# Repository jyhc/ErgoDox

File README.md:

# Information
This repo is a fork of the Ergodox project https://github.com/Ergodox-io/ErgoDox to experiement with PCB modification to support Kailh choc low profile switches. 

Kailh choc footprint taken and modified from https://github.com/ebastler/marbastlib

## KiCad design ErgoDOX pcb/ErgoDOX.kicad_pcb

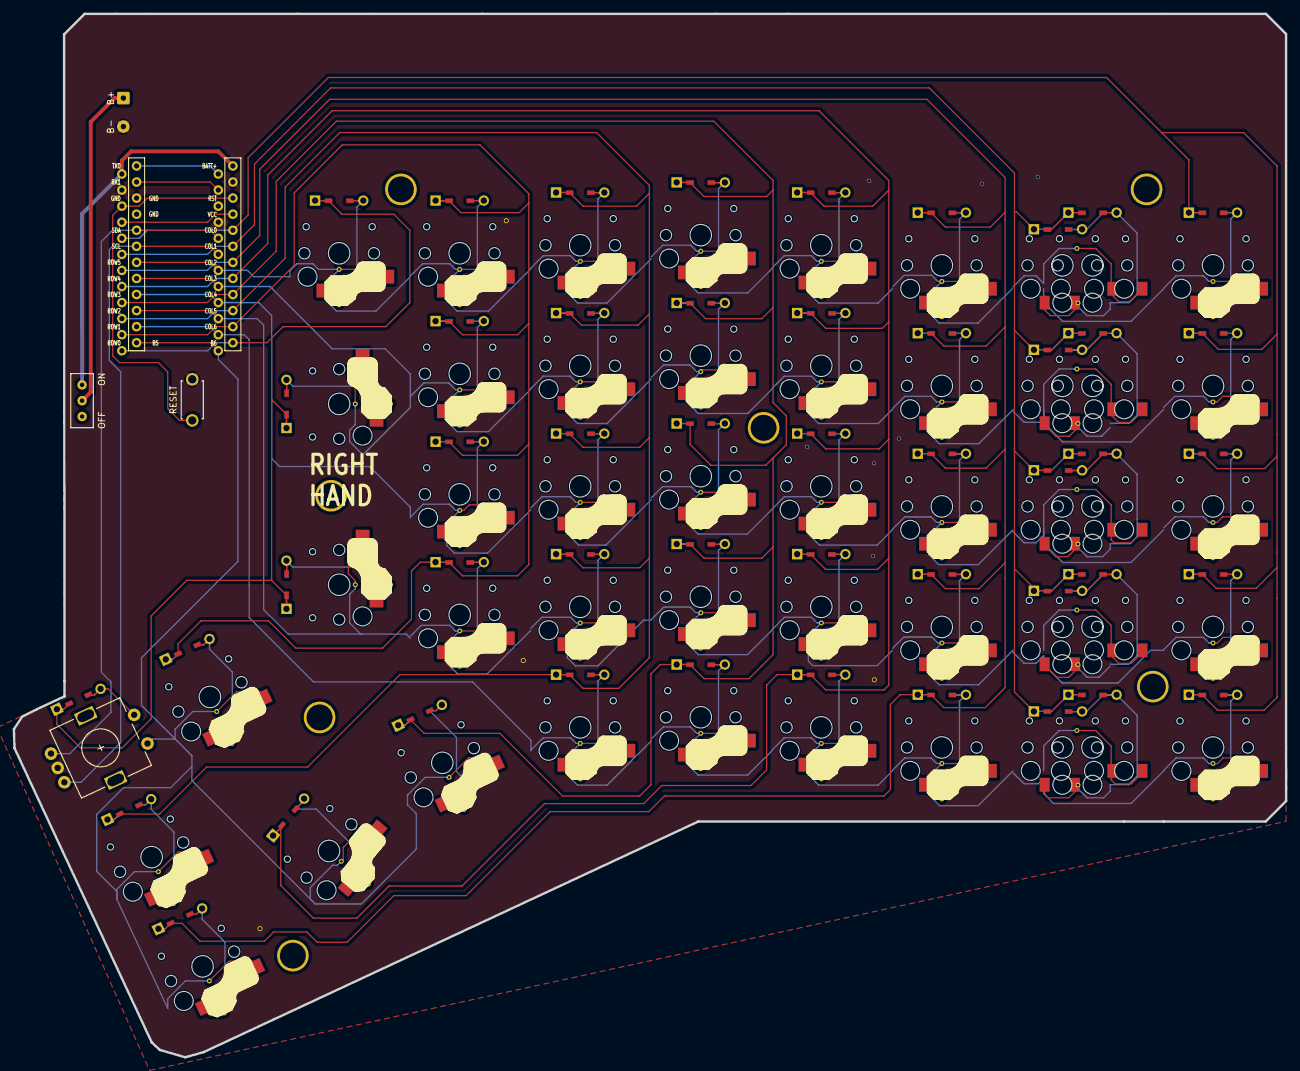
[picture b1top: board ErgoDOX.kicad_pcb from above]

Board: 2 copper layers, 201.1 x 164.9 mm, 51 parts (0 on the bottom side), 62 nets.

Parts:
BATTERY: Battery_Wire_Connector
BSW1: SW_DPDT_x2; SS-12D00
RSW1: SW_Push; ResetSW
STITCHING_VIA: STITCHING_VIA
STITCHING_VIA#2, STITCHING_VIA#3, STITCHING_VIA#4: STITCHING_VIA
SW0:7: SW0:6; RotaryEncoder_Alps_EC11E-Switch_Vertical_H20mm-keebio_modif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
SW0:8: SW0:5; Choc_Hotswap
SW0:9: SW0:4; Choc_Hotswap
SW0:10: SW0:3; Choc_Hotswap
SW0:11: SW0:2; Choc_Hotswap
SW0:12: SW0:1; Choc_Hotswap
SW1:9: SW1:4; Choc_Hotswap
SW1:10: SW1:3; Choc_Hotswap
SW1:11: SW1:2; Choc_Hotswap
SW1:12: SW1:1; Choc_Hotswap
SW1:13: SW1:0; Choc_Hotswap_1u+1.5u
SW2:7: SW2:6; Choc_Hotswap
SW2:8: SW2:5; Choc_Hotswap
SW2:9: SW2:4; Choc_Hotswap
SW2:10: SW2:3; Choc_Hotswap
SW2:11: SW2:2; Choc_Hotswap
SW2:12: SW2:1; Choc_Hotswap
SW2:13: SW2:0; Choc_Hotswap_1u+1.5u
SW3:8: SW3:5; Choc_Hotswap
SW3:9: SW3:4; Choc_Hotswap
SW3:10: SW3:3; Choc_Hotswap
SW3:11: SW3:2; Choc_Hotswap
SW3:12: SW3:1; Choc_Hotswap
SW3:13: SW3:0; Choc_Hotswap_1u+1.5u
SW4:7: SW4:6; Choc_Hotswap
SW4:8: SW4:5; Choc_Hotswap
SW4:9: SW4:4; Choc_Hotswap
SW4:10: SW4:3; Choc_Hotswap
SW4:11: SW4:2; Choc_Hotswap
SW4:12: SW4:1; Choc_Hotswap
SW4:13: SW4:0; Choc_Hotswap_1u+1.5u
SW5:7: SW5:6; Choc_Hotswap
SW5:8: SW5:5; Choc_Hotswap
SW5:9: SW5:4; Choc_Hotswap
SW5:10: SW5:3; Choc_Hotswap
SW5:11: SW5:2; Choc_Hotswap
SW5:12: SW5:1; Choc_Hotswap
SW5:13: SW5:0; Choc_Hotswap_1u+1.5u
SW11, SW11#2, SW11#3, SW11#4, SW11#5: SW_Push; Choc_Hotswap
U1: nice!nano; nicenano

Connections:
1-pad2: SW11#3.2, SW11#3.3
2-pad2: SW11#2.2, SW11#2.3
3-pad2: SW11#5.2, SW11#5.3
4-pad2: SW11.2, SW11.3
5-pad2: SW11#4.2, SW11#4.3
+BATT: BSW1.3, U1.24
/COL0: SW1:13.4 (K), SW2:13.4 (K), SW3:13.4 (K), SW4:13.4 (K), SW5:13.4 (K), U1.19
/COL1: SW0:12.4 (K), SW1:12.4 (K), SW2:12.4 (K), SW3:12.4 (K), SW4:12.4 (K), SW5:12.4 (K), U1.18
/COL4: SW0:9.4 (K), SW1:9.4 (K), SW2:9.4 (K), SW3:9.4 (K), SW4:9.4 (K), SW5:9.4 (K), U1.15
/COL5: SW0:8.4 (K), SW2:8.4 (K), SW3:8.4 (K), SW4:8.4 (K), SW5:8.4 (K), U1.14
/COL6: SW2:7.4 (K), SW4:7.4 (K), SW5:7.4 (K), U1.13
/COL7: SW11.4, SW11#2.4, SW11#3.4, SW11#4.4, SW11#5.4, U1.20
/COL10: SW0:10.4 (K), SW1:10.4 (K), SW2:10.4 (K), SW3:10.4 (K), SW4:10.4 (K), SW5:10.4 (K), U1.16
/COL11: SW0:11.4 (K), SW1:11.4 (K), SW2:11.4 (K), SW3:11.4 (K), SW4:11.4 (K), SW5:11.4 (K), U1.17
/ROW0: SW0:7.S1, SW0:8.1, SW0:9.1, SW0:10.1, SW0:11.1, SW0:12.1, U1.12
/ROW1: SW1:9.1, SW1:10.1, SW1:11.1, SW1:12.1, SW1:13.1, SW11#4.1, U1.11
/ROW2: SW2:7.1, SW2:8.1, SW2:9.1, SW2:10.1, SW2:11.1, SW2:12.1, SW2:13.1, SW11.1, U1.10
/ROW3: SW3:8.1, SW3:9.1, SW3:10.1, SW3:11.1, SW3:12.1, SW3:13.1, SW11#5.1, U1.9
/ROW4: SW4:7.1, SW4:8.1, SW4:9.1, SW4:10.1, SW4:11.1, SW4:12.1, SW4:13.1, SW11#2.1, U1.8
/ROW5: SW5:7.1, SW5:8.1, SW5:9.1, SW5:10.1, SW5:11.1, SW5:12.1, SW5:13.1, SW11#3.1, U1.7
/RST: RSW1.2, U1.22
ENCA: SW0:7.A, U1.5
ENCB: SW0:7.B, U1.6
GND: BATTERY.2, RSW1.1, STITCHING_VIA.GND, STITCHING_VIA#2.GND, STITCHING_VIA#3.GND, STITCHING_VIA#4.GND, SW0:7.C, U1.3, U1.4, U1.23
NET-(BSW1-PAD2): BATTERY.1, BSW1.2
unnamed: SW0:8.2, SW0:8.3 (A)
unnamed: SW0:9.2, SW0:9.3 (A)
unnamed: SW0:10.2, SW0:10.3 (A)
unnamed: SW0:11.2, SW0:11.3 (A)
unnamed: SW0:12.2, SW0:12.3 (A)
unnamed: SW1:9.2, SW1:9.3 (A)
unnamed: SW1:10.2, SW1:10.3 (A)
unnamed: SW1:11.2, SW1:11.3 (A)
unnamed: SW1:12.2, SW1:12.3 (A)
unnamed: SW1:13.2, SW1:13.3 (A)
unnamed: SW2:7.2, SW2:7.3 (A)
unnamed: SW2:8.2, SW2:8.3 (A)
unnamed: SW2:9.2, SW2:9.3 (A)
unnamed: SW2:10.2, SW2:10.3 (A)
unnamed: SW2:11.2, SW2:11.3 (A)
unnamed: SW2:12.2, SW2:12.3 (A)
unnamed: SW2:13.2, SW2:13.3 (A)
unnamed: SW3:8.2, SW3:8.3 (A)
unnamed: SW3:9.2, SW3:9.3 (A)
unnamed: SW3:10.2, SW3:10.3 (A)
unnamed: SW3:11.2, SW3:11.3 (A)
unnamed: SW3:12.2, SW3:12.3 (A)
unnamed: SW3:13.2, SW3:13.3 (A)
unnamed: SW4:7.2, SW4:7.3 (A)
unnamed: SW4:8.2, SW4:8.3 (A)
unnamed: SW4:9.2, SW4:9.3 (A)
unnamed: SW4:10.2, SW4:10.3 (A)
unnamed: SW4:11.2, SW4:11.3 (A)
unnamed: SW4:12.2, SW4:12.3 (A)
unnamed: SW4:13.2, SW4:13.3 (A)
unnamed: SW5:7.2, SW5:7.3 (A)
unnamed: SW5:8.2, SW5:8.3 (A)
unnamed: SW5:9.2, SW5:9.3 (A)
unnamed: SW5:10.2, SW5:10.3 (A)
unnamed: SW5:11.2, SW5:11.3 (A)
unnamed: SW5:12.2, SW5:12.3 (A)
unnamed: SW5:13.2, SW5:13.3 (A)

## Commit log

2022-05-21 test replace with choc switch
2022-05-22 add and modified Kailh choc footprint from https://github.com/ebastler/marbastlib
2022-05-22 replace first row switches
2022-05-23 finish replacing all switches
2022-05-28 add usb c footprint file from https://github.com/ai03-2725/Type-C.pretty
2022-05-29 change to usb c single side
2022-06-12 update with reroute to use nice nano v2 and choc hotswap footprint
2022-06-13 good for prod
2022-07-03 update holes
2022-07-20 create 1u1.5u footprint
2022-07-22 Revert "create 1u1.5u footprint"
    This reverts commit 3dfe5ebad1ff0df9ab9336540538172015dde196.
2022-08-06 add encoder switch
2022-08-07 finish top and bottom plates
2022-08-08 combined top design
2024-08-06 update trace widths
2024-08-07 upload gerber

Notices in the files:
parts and their libraries:
Licensed under the MIT License - Copyright (c) 2019 foostan - Based on https://github.com/foostan/crkbd/tree/main/corne-chocolate/pcb
Licensed under the MIT License - Copyright (c) 2020 foostan, Based on https://github.com/foostan/kbd/blob/master/kicad-footprints/kbd.pretty/ProMicro_v2.kicad_mod
